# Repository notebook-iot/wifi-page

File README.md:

# wifi-page
WiFi enabled sidecar board enabling embedded devices to communicate with the cloud

## Known Issues in v1r1

- If you aren't careful when scratching the trace to switch the power path, there could be backfeed. We experienced the LDO drawing too much current despite the other pins being bridged, and the voltage on the power rail dropped to ~1V.
- There is no pull-down resistor on IO46, which is one of the strapping pins for flashing over UART using the joint download mode. We fixed this temporarily by tacking a wire between IO46 and GND.

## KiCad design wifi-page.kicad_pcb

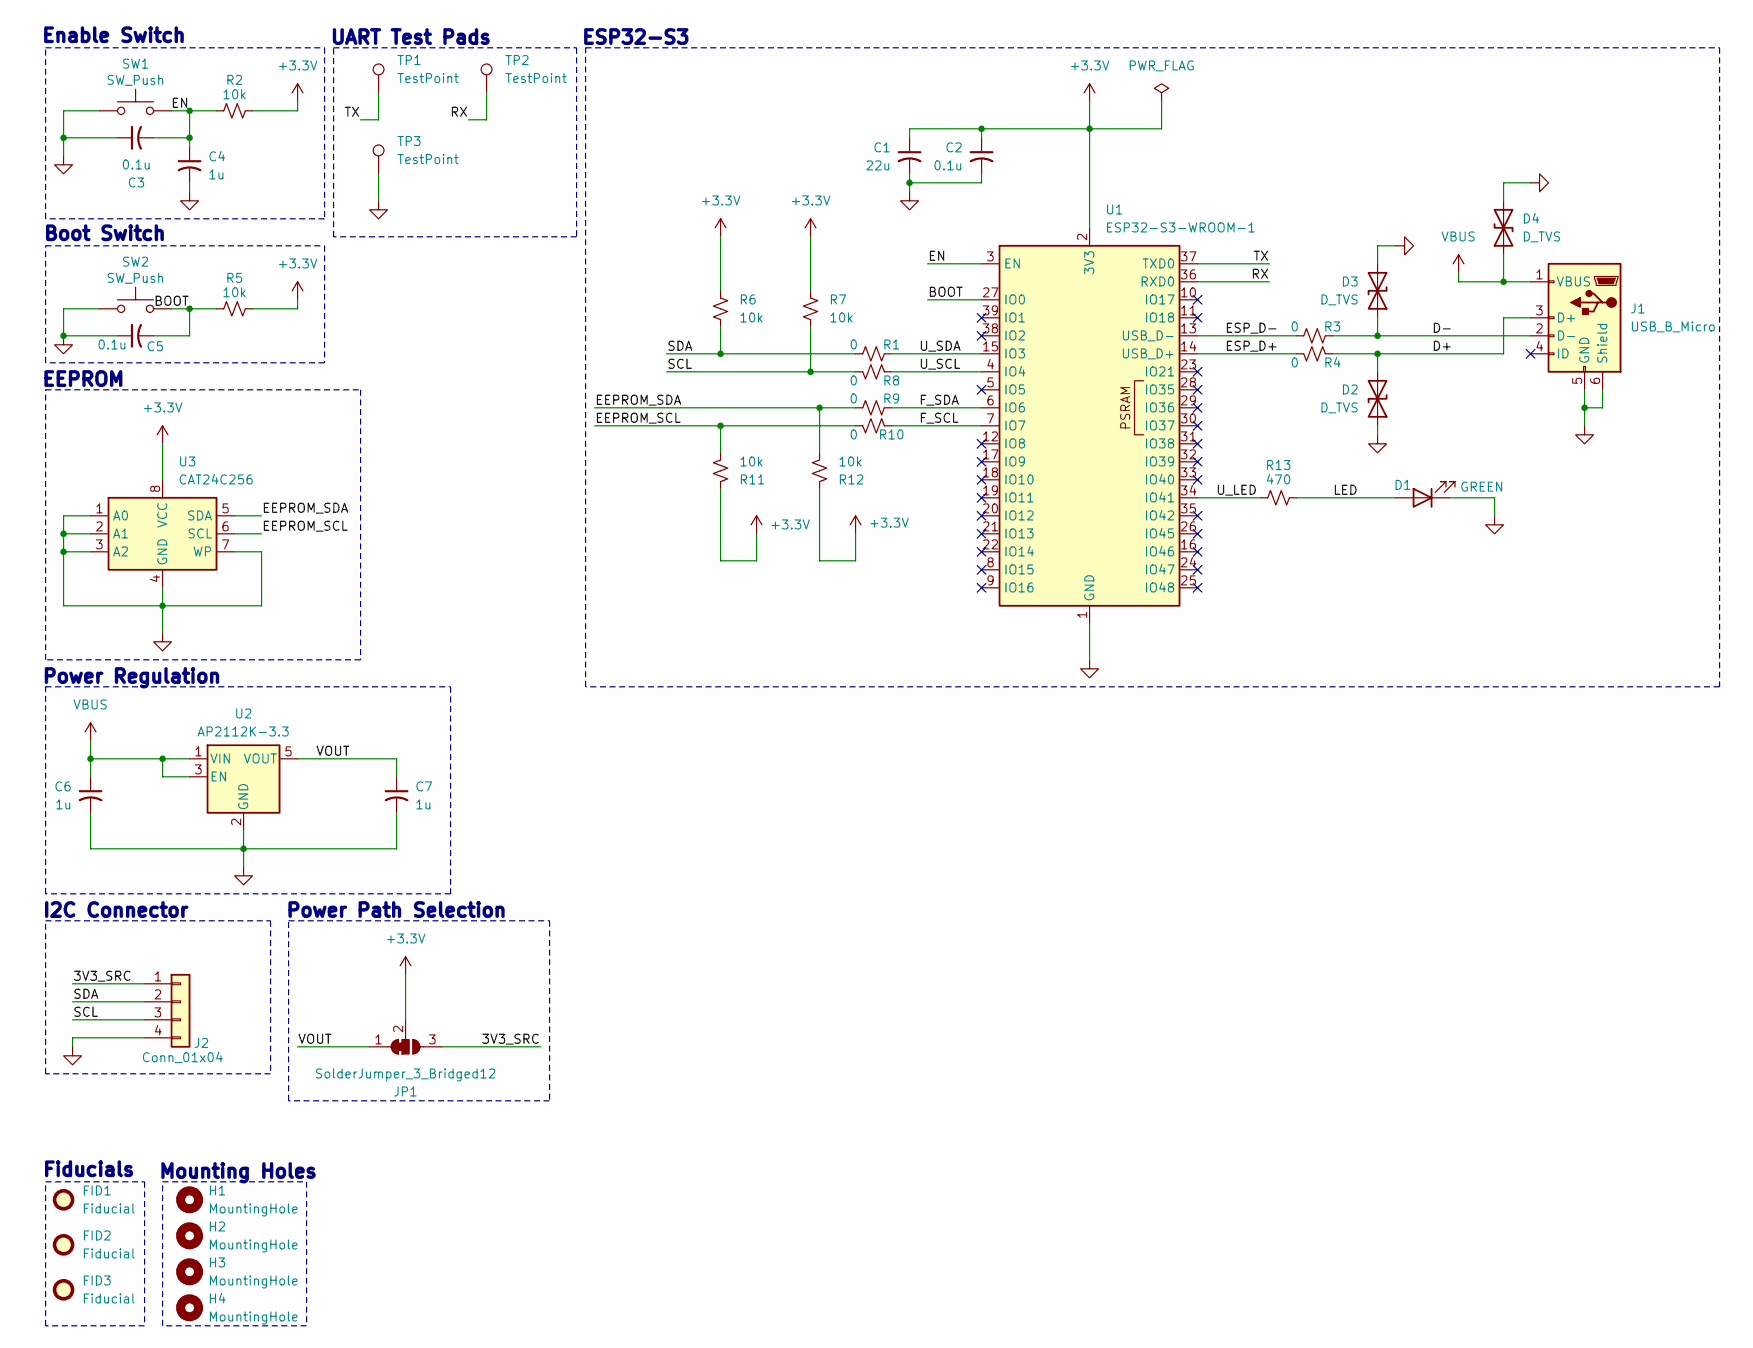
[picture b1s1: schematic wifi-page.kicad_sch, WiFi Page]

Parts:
C1: 22u; C_0805_2012Metric
C2, C3, C5: 0.1u; C_0805_2012Metric
C4, C6, C7: 1u; C_0805_2012Metric
D1: GREEN; LED_0805_2012Metric
D2, D3, D4: D_TVS; D_SOD-323
FID1, FID2, FID3: Fiducial; Fiducial_1mm_Mask2mm
H1, H2, H3, H4: MountingHole; MountingHole_2mm
J1: USB_B_Micro; USB_Micro-AB_Molex_47590-0001
J2: Conn_01x04; PinSocket_1x04_P2.54mm_Vertical
JP1: SolderJumper_3_Bridged12; SolderJumper-3_P1.3mm_Bridged12_RoundedPad1.0x1.5mm_NumberL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
R1, R3, R4, R8, R9, R10: 0; R_0805_2012Metric
R2, R5, R6, R7, R11, R12: 10k; R_0805_2012Metric
R13: 470; R_0805_2012Metric
SW1, SW2: SW_Push; SW_Push_1P1T_NO_CK_KMR2
TP1, TP2, TP3: TestPoint; TestPoint_THTPad_D1.5mm_Drill0.7mm
U1: ESP32-S3-WROOM-1
U2: AP2112K-3.3; SOT-23-5
U3: CAT24C256; SOIC-8_3.9x4.9mm_P1.27mm

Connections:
+3.3V: C1.1, C2.1, JP1.2 (C), R2.2, R5.2, R6.1, R7.1, R11.1, R12.1, U1.2 (3V3), U3.8 (VCC)
/3V3_SRC: J2.1, JP1.3 (B)
/BOOT: C5.2, R5.1, SW2.2, U1.27 (IO0)
/D+: D2.2 (A2), J1.3 (D+), R4.2
/D-: D3.1 (A1), J1.2 (D-), R3.2
/EEPROM_SCL: R10.1, R11.2, U3.6 (SCL)
/EEPROM_SDA: R9.1, R12.2, U3.5 (SDA)
/EN: C3.2, C4.1, R2.1, SW1.2, U1.3 (EN)
/ESP_D+: R4.1, U1.14 (USB_D+)
/ESP_D-: R3.1, U1.13 (USB_D-)
/F_SCL: R10.2, U1.7 (IO7)
/F_SDA: R9.2, U1.6 (IO6)
/LED: D1.2 (A), R13.2
/RX: TP2.1, U1.36 (RXD0)
/SCL: J2.3, R7.2, R8.1
/SDA: J2.2, R1.1, R6.2
/TX: TP1.1, U1.37 (TXD0)
/U_LED: R13.1, U1.34 (IO41)
/U_SCL: R8.2, U1.4 (IO4)
/U_SDA: R1.2, U1.15 (IO3)
/VOUT: C7.1, JP1.1 (A), U2.5 (VOUT)
GND: C1.2, C2.2, C3.1, C4.2, C5.1, C6.2, C7.2, D1.1 (K), D2.1 (A1), D3.2 (A2), D4.2 (A2), J1.5 (GND), J1.6 (Shield), J2.4, SW1.1, SW2.1, TP3.1, U1.1 (GND), U1.40 (GND), U1.41 (GND), U2.2 (GND), U3.1 (A0), U3.2 (A1), U3.3 (A2), U3.4 (GND), U3.7 (WP)
VBUS: C6.1, D4.1 (A1), J1.1 (VBUS), U2.1 (VIN), U2.3 (EN)

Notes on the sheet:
I2C Connector
Mounting Holes
EEPROM
Power Regulation
Enable Switch
Power Path Selection
UART Test Pads
ESP32-S3
Fiducials
Boot Switch

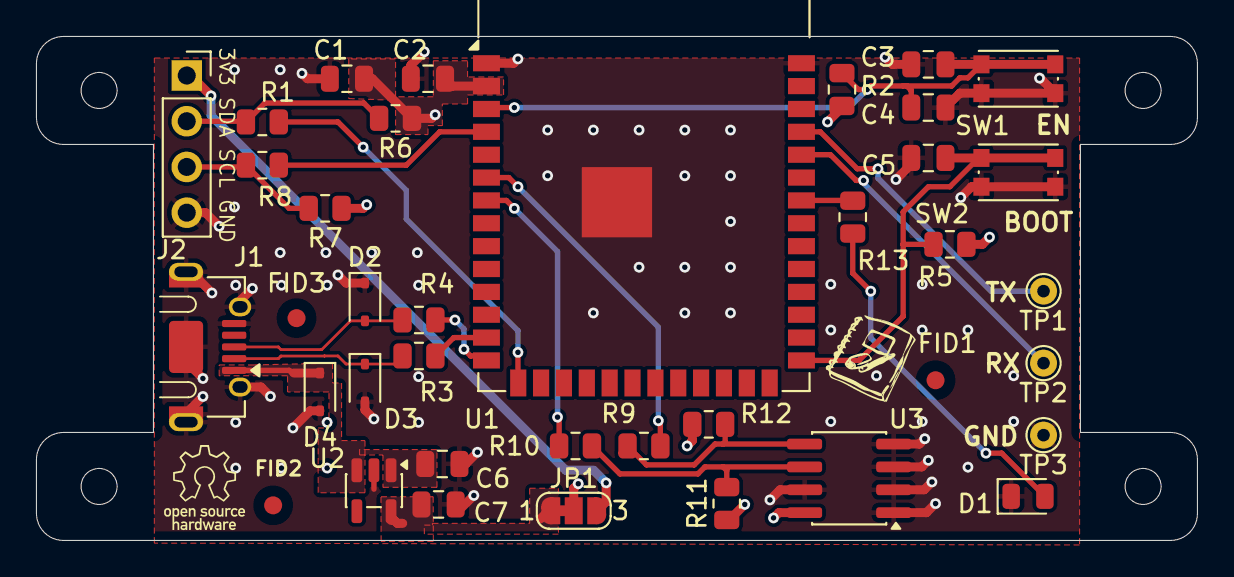
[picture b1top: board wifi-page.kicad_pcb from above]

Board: 4 copper layers, 64.5 x 28.0 mm, 42 parts (0 on the bottom side), 23 nets.

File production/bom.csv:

Designator,Footprint,Quantity,Value,LCSC Part #
C1,0805,1,22u,
"C2, C3, C5",0805,3,0.1u,
"C4, C6, C7",0805,3,1u,
D1,0805,1,GREEN,
"D2, D3, D4",D_SOD-323,3,D_TVS,
J1,USB_Micro-AB_Molex_47590-0001,1,USB_B_Micro,
J2,PinSocket_1x04_P2.54mm_Vertical,1,Conn_01x04,
"R1, R10, R3, R4, R8, R9",0805,6,0,
"R11, R12, R2, R5, R6, R7",0805,6,10k,
R13,0805,1,470,
"SW1, SW2",SW_Push_1P1T_NO_CK_KMR2,2,SW_Push,
"TP1, TP2, TP3",TestPoint_THTPad_D1.5mm_Drill0.7mm,3,TestPoint,
U1,ESP32-S3-WROOM-1,1,ESP32-S3-WROOM-1,
U2,SOT-23-5,1,AP2112K-3.3,
U3,SOIC-8_3.9x4.9mm_P1.27mm,1,CAT24C256,

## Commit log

2026-03-22 add initial revision
2026-03-22 update silkscreen
2026-05-03 add known issues
